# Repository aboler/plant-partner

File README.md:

# plant-partner

Plant Partner repo. for CEN4908c

- **Contributors**: Nicholas Cimino, Aspen Boler, Sabrina Luu, Carter Kreis, Fernando Amado-Pupo
- [Project link](https://github.com/users/aboler/projects/1)

### Notes for adding code and time reports

- Please create a new branch to develop off of main
  - main remains as a minimum viable product branch available
  - Allows PR's to be made for adding to dev so group members can review code made
- Add reports for any changes/development work done in a day in main branch
  - Make reports in Documentation/Reports in relevant timesheet

## Meeting Times

- Meet weekly for ~15 minutes after every client meeting to ensure we're staying on track

## Completed Work

### Hardware Release

Please see ``Documentation/Diagrams``, ``Documentation/Circuits``, and ``Documentation/pcbDesign`` for current hardware designed, built, and used for testing

### Software Release

<ins>For ESP32 (in VSCode):</ins>

1. Run ``git clone recurse-submodules git@github.com:aboler/plant-partner.git``
   - This will clone the base plant-partner and esp-idf Github repositories using ssh
2. Download the ESP-IDF Extension
3. After you install the extension, the  should appear in the VS Code Activity bar (left side set of icons). When you click the Espressif icon, you can see a list of basic commands provided by this extension.
4. From the command list, select Configure ESP-IDF Extension or press F1 and type “Configure ESP-IDF Extension”. After, choose the ESP-IDF: Configure ESP-IDF Extension option.
5. Choose Express. Select Github for the download server.
6. For “Select ESP-IDF version” select “Find ESP-IDF in your system”
7. For “Enter ESP-IDF directory (IDF_PATH):” click the folder icon and within the Github Repository select /plant-partner/microSrc/submodules/esp-idf
8. For “Enter ESP-IDF Tools directory (IDF_TOOLS_PATH):” select the default location or wherever you prefer
   - Make sure that IDF_TOOLS_PATH had no spaces and is not in the Github Repo
9. If your operating system is MacOS/Linux, choose the system Python executable to create ESP-IDF virtual environment inside ESP-IDF Tools and install ESP-IDF Python package there
10. Click Install
11. If everything is installed correctly, you will see a message that all settings have been configured

In Powershell or a Linux terminal preferably:

1. Run ``cd microSrc``
2. Connect an ESP-32 into computer
3. Setup ESP-IDF and flash ESP-32 by running ``python esp.py -p PORT``
   - You may need to use python3 instead of python
   - PORT will be something like COM3 for Windows and /dev/ttyUSB0 for Ubuntu

<ins>For Backend + Database:</ins>

1. Navigate to ``backEndSrc/``
2. Start up the backend server by running ``npm start``, server will be running once these messages are displayed on the terminal
   - "Connected to MongoDB"
   - "Server running on port 8000"

<ins>For Frontend Application:</ins>

In Bash or Powershell

1. Run `cd frontEndSrc`
2. Run `cd frontend`
3. Run `flutter emulators –launch Medium_Phone_API_36.1`
4. Run `flutter pub get`
   * This command is to pull the dependencies
5. Run `flutter run`

### Pre-Alpha Build

- Ability to control GPIO Pins w/ ESP32.
  - i.e. controlling an external light source
  - Existing interfaces that allow modular control for project's purposes
- ADC data acquisition w/ ESP32
  - i.e. reading in value from photoresistor
  - Existing interfaces that allow modular control for project's purposes
- Developed basic structure to collect plant data from sensors
  - 3 uint16_t variables for collecting light, moisture, and nutrient data
- Breadboard implementation of our hardware/software
  - External photoresistor/LED circuit
- Frontend initial skeleton set up for mobile Android app interface
  - Configured Flutter environment and Android Emulator
  - Built a persistent bottom navigation bar (Tasks, Home, Settings)
  - Developed placeholder screens for each tab
  - Tested UI flow and verified emulator functionality
- Implemented locally-hosted database and backend API source code with basic functions
  - Set up MongoDB database that can be hosted locally, currently stores one JSON data model
  - Created Backend App source code with an API via Express.JS that allows for communication with the backend server and database
  - Organized the source code into folders for function controllers, JSON data models, and CRUD routes for easy addition of new functionality

### Prototype Build

- Ability to configure input GPIO Pins w/ ESP32
- Ability to generate a PWM signal
  - i.e. controlling a water pump omtor
- Modularized ADC data acquisition
  - Allows for configuration for both photoresistor and mositure sensor
- Modified breadboard implementation
  - Developed switch circuit to determine when to sample connected sensors/actuate components
  - e.g. water pump control, photoresistor and moisture sensing, LED actuation
- Ability to connect ESP32 to Wi-Fi
  - Allows new plant data to be sent to the database
- Created a test plant on the database
- Connected application and database so application can receive and display plant data to the Home tab
- Created a update button that allows application to display newly updated data from the database
- Beginnings of a PCB to replace external wiring has been started and posted to the repository
- Migrate database to the cloud via MongoDB atlas to allow for easier testing

### Alpha Build

- General clean up/organization in the code
- Modified ADC to be initialized through one function
- Modified main microcontroller loop to activate from one signal (currently a switch)
  - Reads all sensors
  - Activates actuators if needed
  - Sends data to database over Wi-Fi
- Created more permanent physical set up
  - Liquid tanks
  - Motor pumps in liquid tanks with elongated wires
  - Central cup to act as a pot
  - External carrying mechanism to more easily keep everything together
  - Smaller external circuit board
  - DAD program to act as switch, external LED, and proof that fertilizer motor activates when needed

### Beta Build

- Integrated MQTT messages to be sent from database/app. to initiate microcontroller main loop
  - ```plant_partner/act_tog_en```: toggle autocare enable
  - "plant_partner/ack"
    - w/ ```water``` msg.: actuate water pump, read moisture sensor, then report back data to the app.
    - w/ ```light``` msg.: toggle external LED, read photoresistor, then report back data to the app.
    - w/ ```nutrients``` msg.: actuate fertilizer pump
    - no message: read all of the sensors then report the data to the app.
      - If autocare enabled, then also actuate sensors based on if data requires it
- Finished and ordered PCB
- Soldered temporary physical board
- Instantiated and connected rough physical set up assembled in alpha build
- Added additional user features in the application:
  - Ability to toggle autocare and sync it with the microcontroller
  - button for actuating specific actuators
- Developed MQTT message functionality in the database
  - Time-based sample commands
  - Ability for specific actuation 

## Project Architecture

The ESP32 board is set up to interface with sensors to collect real-time environmental and system data. Currently, the microcontroller waits until it receives particular messages through an MQTT client. Depending on the message it can do the following: 1) toggle if autocare is enabled or disabled, 2) samples sensors, communicate data to the app., and actuate (if autocare on), 3) actuate a specific actuator (i.e. LED, water pump, fertilizer pump). These messages are currently being sent from the application while the sensor data is being communicated to the database.

The sensor readings can be reported to the database and displayed on a mobile application, providing users with remote monitoring. To update the data shown on the application, users must press the update button available in the Home tab. Additionally, there's a scheduling tab available where the autocare feature can be toggled as well as three actuator specific buttons for directly affecting specific devices.

### File Structure Summary

- ``microsrc`` : directory containing relevant ESP32 code
  - ``scripts`` : directory containing scripts necessary for setting up ESP-IDF dependencies and environment for device
  - ``src`` : directory containing all developed code for the program and a CMakeLists.txt to help compile
    - ``main`` : contains main program for ESP32 and CMakeLists.txt compiling developed code
    - ``dataTypes`` : contains code defining common data types created for the project, like plantData
    - ``peripherals`` : code for modularizing intercations with certain peripheral systems, like ADC, GPIO, and PWM
    - ``wifi`` : code for implementing wifi communication in the esp32
  - ``submodules`` : directory containing other repositories utilized within the main code
    - ``esp-idf`` : submodule containing examples and ESP32 interfaces in c
  - ``esp.py`` : Python script which can setup, build, flash, and/or monitor ESP-32
- ``backEndSrc`` : directory containing relevant backend code

  - ``controller`` : directory containing code for controllers that implement backend API CRUD functions for the server
    - ``sensorController.js`` : code for implementing CRUD functions that work with JSON data of the Sensor model
  - ``model`` : directory containing code for JSON data models to be used by the backend server and MongoDB database
    - ``sensorModel.js`` : code for creating the JSON Sensor data model
  - ``routes`` : directory containing code for the API's routes that allow CRUD functions to be accessed via URI in an HTTP request
    - ``sensorRoute.js`` : code for the routes that make use of functions that work with the Sensor JSON data model
  - ``node_modules`` : directory containing the node.js dependencies needed to create the backend code
  - ``.env`` : file that holds environment variables to be used by the main code of the backend server, app.js
  - ``app.js`` : the main code of the backend server, connecting to the mongoDB database, linking the routes, and locally hosting server
  - ``package-lock.json`` : the package-lock file for all the node package dependencies needed for the backend server
  - ``package.json`` : the package file listing the basic details and dependencies of the backend server project
- ``frontEndSrc`` : directory containing all Flutter/Dart source code for the mobile application.

  - ``lib``: root directory for all application logic, user interface screens, and services.
    - ``main``: application entry point; initializes the app and launches the bottom navigation shell
    - `nav.dart/dashboard_nav.dart`: bottom navigation bar widget and screen routing logic
    - ``views/``: directory containing all primary UI pages
      - `homeView.dart`: displays live plant sensor data from MongoDB and includes refresh functionality.
      - `taskView.dart/settingsView.dart:` placeholder screen for task/scheduling and user settings
      - `addPlantView.dart`: screen for adding new plants (prototype stage)
    - `services/`: directory for backend communication modules
      - `remote_service.dart`: handles HTTP requests to the backend
    - `plant.dart`: types data model used to decode JSON plant objects from the database

- ``Documentation`` : directory containing relevant project documentation
  - ``Circuits`` : directory containing relevant circuits created during development
  - ``ClassSubmissions`` : directory containing a file with the link to the Google Drive folder containing all of our report work/submissions
  - ``Contributions`` : directory containing all members' timesheet records
  - ``Datasheets`` : directory containing schematics to reference for our current materials being used
  - ``Diagrams`` : directory containing relevant diagrams created during development
  - ``Materials`` : directory containing documentation related to materials, such as which items were purchased and from where
  - ``Mosquitto`` : directory containing configuration files needed to successfully run mosquitto with our program
  - ``Research`` : directory containing research collected during the project, such as how to set up a coding environment for the ESP32
  - ``pcbDesign`` : directory containing work dones towards designing/building our project's PCB

## How to Use esp.py

PORT: This is USB port that the ESP-32 is connected to. For Windows, it should be COM3 or something similar. For Ubuntu, it should be ``/dev/ttyUSB0`` or something similar. Be aware, that if the Port is not automatically detected (usually Windows) you may have to install a driver being Silicon Labs CP210x or FTDI.

- Default: ``python esp.py -p PORT``
  - This will run the necessary setup scripts to install the ESP-IDF dependencies then build, flash, and monitor the ESP-32 at PORT
- Build: ``python esp.py build``
  - This will only build the current code under microSrc/src
- Flash: ``python esp.py flash -p PORT``
  - This will build and flash the current code under microSrc/src onto the ESP-32 at the connected Port
- Monitor: ``python esp.py monitor -p PORT``
  - This will monitor the ESP-32 at the connected Port and fill the terminal with any outputs from the ESP-32
- Clean: ``python esp.py clean``
  - This will delete any build artifacts

N.B. You may have to use python3 instead of python

## Current Bugs:

The system is in a development state with only base-level functionality implemented. No bugs reported

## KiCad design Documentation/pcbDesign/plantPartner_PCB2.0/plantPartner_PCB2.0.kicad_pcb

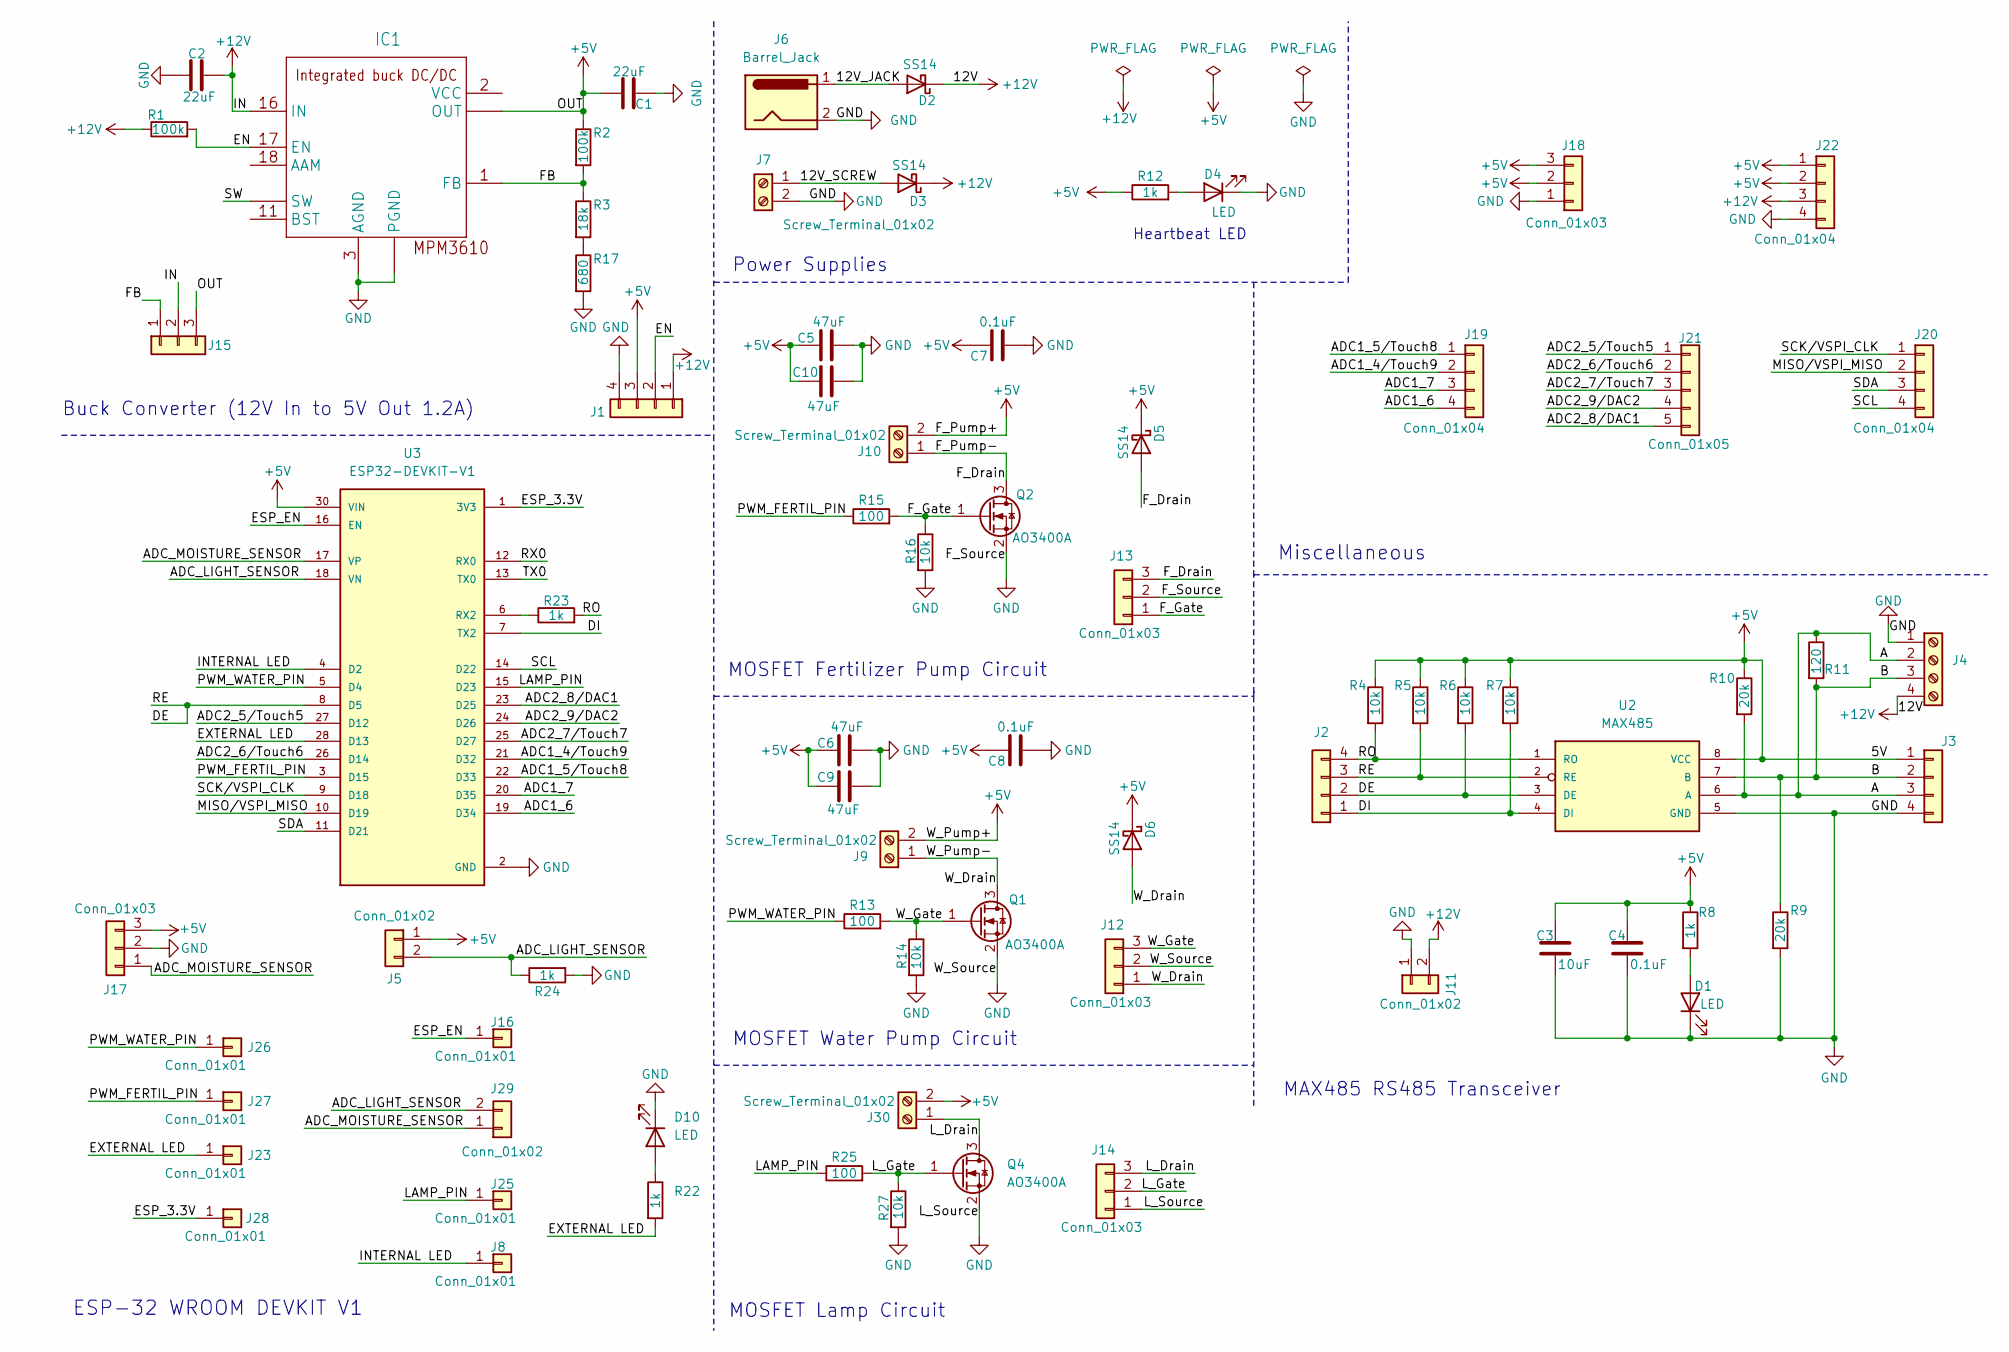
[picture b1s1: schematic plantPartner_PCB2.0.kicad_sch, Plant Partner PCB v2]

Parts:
C1, C2: 22uF; C_0603_1608Metric
C3: 10uF; C_0402_1005Metric
C4: 0.1uF; C_0402_1005Metric
C5, C6, C9, C10: 47uF; C_0805_2012Metric
C7, C8: 0.1uF; C_0603_1608Metric
D1, D4, D10: LED; LED_0603_1608Metric
D2, D3, D5, D6: SS14; D_SMA
IC1: MPM3610
J1, J2, J3, J19, J20, J22: Conn_01x04; PinHeader_1x04_P2.54mm_Vertical
J4: Screw_Terminal_01x04; TerminalBlock_Phoenix_MPT-0,5-4-2.54_1x04_P2.54mm_Horizontal
J5, J11, J29: Conn_01x02; PinHeader_1x02_P2.54mm_Vertical
J6: Barrel_Jack; BarrelJack_GCT_DCJ200-10-A_Horizontal
J7, J9, J10, J30: Screw_Terminal_01x02; TerminalBlock_Phoenix_MPT-0,5-2-2.54_1x02_P2.54mm_Horizontal
J8, J16, J23, J25, J26, J27, J28: Conn_01x01; PinHeader_1x01_P2.54mm_Vertical
J12, J13, J14, J15, J17, J18: Conn_01x03; PinHeader_1x03_P2.54mm_Vertical
J21: Conn_01x05; PinHeader_1x05_P2.54mm_Vertical
Q1, Q2, Q4: AO3400A; SOT-23
R1, R2: 100k; R_0402_1005Metric
R3: 18k; R_0603_1608Metric
R4, R5, R6, R7, R14, R16, R27: 10k; R_0402_1005Metric
R8, R12, R22, R23, R24: 1k; R_0402_1005Metric
R9, R10: 20k; R_0402_1005Metric
R11: 120; R_0402_1005Metric
R13, R15, R25: 100; R_0402_1005Metric
R17: 680; R_0603_1608Metric
U2: MAX485; SO08
U3: ESP32-DEVKIT-V1; MODULE_ESP32_DEVKIT_V1; PARTREV N/A

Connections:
+5V: C1.1, C3.1, C4.1, C5.1, C6.1, C7.1, C8.1, C9.1, C10.1, D5.1 (K), D6.1 (K), IC1.7 (OUT), IC1.8 (OUT), IC1.9 (OUT), J1.3, J3.1, J5.1, J9.2, J10.2, J15.3, J17.3, J18.2, J18.3, J22.1, J22.2, J30.2, R2.1, R4.1, R5.1, R6.1, R7.1, R8.1, R10.1, R12.1, U2.8 (VCC), U3.30 (VIN)
+12V: C2.1, D2.1 (K), D3.1 (K), IC1.16 (IN), J1.1, J4.4, J11.2, J15.2, J22.3, R1.1
/12V_JACK: D2.2 (A), J6.1
/12V_SCREW: D3.2 (A), J7.1
/A: J3.3, J4.2, R10.2, R11.1, U2.6 (A)
/ADC1_4/Touch9: J19.2, U3.21 (D32)
/ADC1_5/Touch8: J19.1, U3.22 (D33)
/ADC1_6: J19.4, U3.19 (D34)
/ADC1_7: J19.3, U3.20 (D35)
/ADC2_5/Touch5: J21.1, U3.27 (D12)
/ADC2_6/Touch6: J21.2, U3.26 (D14)
/ADC2_7/Touch7: J21.3, U3.25 (D27)
/ADC2_8/DAC1: J21.5, U3.23 (D25)
/ADC2_9/DAC2: J21.4, U3.24 (D26)
/ADC_LIGHT_SENSOR: J5.2, J29.2, R24.1, U3.18 (VN)
/ADC_MOISTURE_SENSOR: J17.1, J29.1, U3.17 (VP)
/B: J3.2, J4.3, R9.1, R11.2, U2.7 (B)
/DE: J2.2, J2.3, R5.2, R6.2, U2.2 (RE), U2.3 (DE), U3.8 (D5)
/DI: J2.1, R7.2, U2.4 (DI), U3.7 (TX2)
/EN: IC1.17 (EN), J1.2, R1.2
/ESP_3.3V: J28.1, U3.1 (3V3)
/ESP_EN: J16.1, U3.16 (EN)
/EXTERNAL LED: J23.1, R22.2, U3.28 (D13)
/FB: IC1.1 (FB), J15.1, R2.2, R3.1
/F_Drain: D5.2 (A), J10.1, J13.3, Q2.3 (D)
/F_Gate: J13.1, Q2.1 (G), R15.2, R16.1
/INTERNAL LED: J8.1, U3.4 (D2)
/LAMP_PIN: J25.1, R25.1, U3.15 (D23)
/L_Drain: J14.3, J30.1, Q4.3 (D)
/L_Gate: J14.2, Q4.1 (G), R25.2, R27.1
/MISO/VSPI_MISO: J20.2, U3.10 (D19)
/PWM_FERTIL_PIN: J27.1, R15.1, U3.3 (D15)
/PWM_WATER_PIN: J26.1, R13.1, U3.5 (D4)
/RO: J2.4, R4.2, R23.2, U2.1 (RO)
/RX0: U3.12 (RX0)
/SCK/VSPI_CLK: J20.1, U3.9 (D18)
/SCL: J20.4, U3.14 (D22)
/SDA: J20.3, U3.11 (D21)
/SW: IC1.4 (SW), IC1.5 (SW), IC1.6 (SW)
/TX0: U3.13 (TX0)
/W_Drain: D6.2 (A), J9.1, J12.1, Q1.3 (D)
/W_Gate: J12.3, Q1.1 (G), R13.2, R14.1
GND: C1.2, C2.2, C3.2, C4.2, C5.2, C6.2, C7.2, C8.2, C9.2, C10.2, D1.1 (K), D4.1 (K), D10.1 (K), IC1.3 (AGND), IC1.12 (PGND), IC1.13 (PGND), IC1.14 (PGND), J1.4, J3.4, J4.1, J6.2, J7.2, J11.1, J12.2, J13.2, J14.1, J17.2, J18.1, J22.4, Q1.2 (S), Q2.2 (S), Q4.2 (S), R9.2, R14.2, R16.2, R17.2, R24.2, R27.2, U2.5 (GND), U3.2 (GND), U3.29 (GND)
unnamed: D1.2 (A), R8.2
unnamed: D4.2 (A), R12.2
unnamed: D10.2 (A), R22.1
unnamed: R3.2, R17.1
unnamed: R23.1, U3.6 (RX2)

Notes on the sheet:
Heartbeat LED
Power Supplies
ESP-32 WROOM DEVKIT V1
Miscellaneous
MAX485 RS485 Transceiver
Buck Converter (12V In to 5V Out 1.2A)
MOSFET Water Pump Circuit
MOSFET Fertilizer Pump Circuit
MOSFET Lamp Circuit

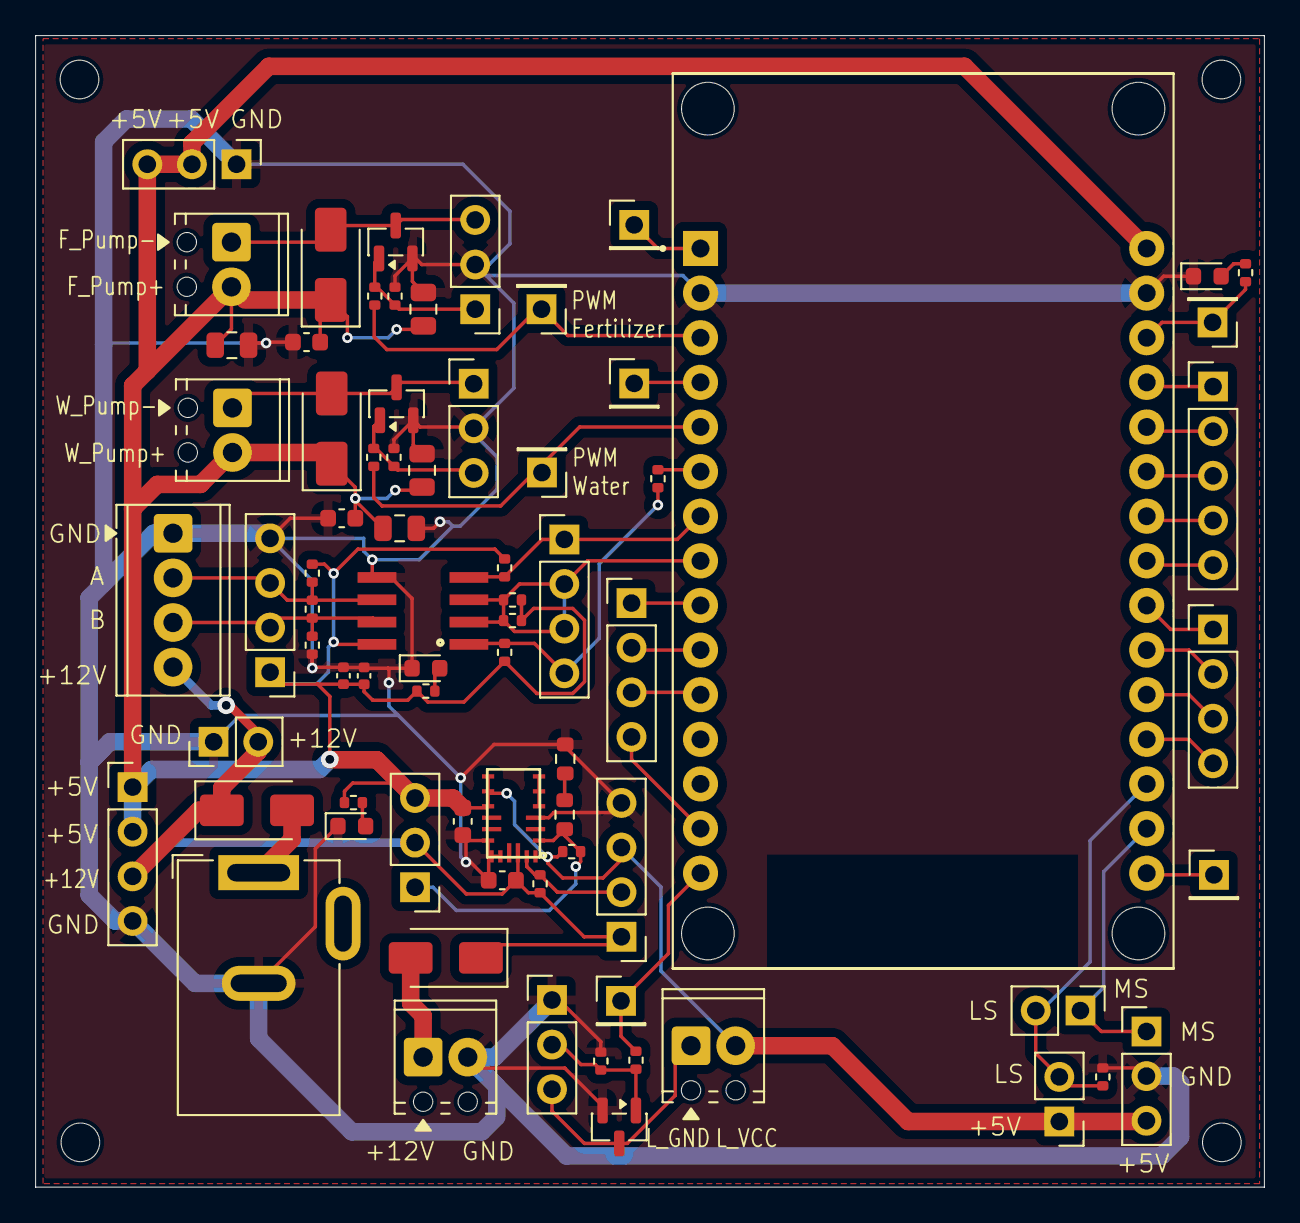
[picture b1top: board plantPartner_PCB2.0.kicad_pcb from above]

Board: 2 copper layers, 70.0 x 65.5 mm, 74 parts (0 on the bottom side), 46 nets.

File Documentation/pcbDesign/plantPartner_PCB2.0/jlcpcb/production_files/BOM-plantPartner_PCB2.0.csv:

Comment,Designator,Footprint,LCSC,Quantity
0.1uF,"C7,C8",C_0603_1608Metric,C14663,2
0.1uF,C4,C_0402_1005Metric,C1525,1
100,"R13,R15,R25",R_0402_1005Metric,C25076,3
100k,"R1,R2",R_0402_1005Metric,C25741,2
10k,"R14,R16,R27,R4,R5,R6,R7",R_0402_1005Metric,C25744,7
10uF,C3,C_0402_1005Metric,C15525,1
120,R11,R_0402_1005Metric,C25079,1
18k,R3,R_0603_1608Metric,C25810,1
1k,"R12,R22,R23,R24,R8",R_0402_1005Metric,C11702,5
20k,"R10,R9",R_0402_1005Metric,C25765,2
220uF,"C5,C6",C_0603_1608Metric,C2163637,2
22uF,"C1,C2",C_0603_1608Metric,C59461,2
680,R17,R_0603_1608Metric,C23228,1
AO3400A,"Q1,Q2,Q4",SOT-23,C20917,3
LED,"D1,D10,D4",LED_0603_1608Metric,C2286,3
MAX485,U2,SO08,C19738,1
MPM3610,IC1,MPM3610,C5173872,1
SS14,"D2,D3,D5,D6",D_SMA,C2480,4
ESP32-DEVKIT-V1,U3,MODULE_ESP32_DEVKIT_V1,,1
Screw_Terminal_01x02,J30,"TerminalBlock_Phoenix_MPT-0,5-2-2.54_1x02_P2.54mm_Horizontal",,1
Conn_01x02,J29,PinHeader_1x02_P2.54mm_Vertical,,1
Conn_01x01,J28,PinHeader_1x01_P2.54mm_Vertical,,1
Conn_01x01,J27,PinHeader_1x01_P2.54mm_Vertical,,1
Conn_01x01,J26,PinHeader_1x01_P2.54mm_Vertical,,1
Conn_01x01,J25,PinHeader_1x01_P2.54mm_Vertical,,1
Conn_01x01,J23,PinHeader_1x01_P2.54mm_Vertical,,1
Conn_01x04,J22,PinHeader_1x04_P2.54mm_Vertical,,1
Conn_01x05,J21,PinHeader_1x05_P2.54mm_Vertical,,1
Conn_01x04,J20,PinHeader_1x04_P2.54mm_Vertical,,1
Conn_01x03,J17,PinHeader_1x03_P2.54mm_Vertical,,1
Conn_01x01,J16,PinHeader_1x01_P2.54mm_Vertical,,1
Conn_01x02,J11,PinHeader_1x02_P2.54mm_Vertical,,1
Screw_Terminal_01x02,J10,"TerminalBlock_Phoenix_MPT-0,5-2-2.54_1x02_P2.54mm_Horizontal",,1
Screw_Terminal_01x02,J9,"TerminalBlock_Phoenix_MPT-0,5-2-2.54_1x02_P2.54mm_Horizontal",,1
Conn_01x01,J8,PinHeader_1x01_P2.54mm_Vertical,,1
Screw_Terminal_01x02,J7,"TerminalBlock_Phoenix_MPT-0,5-2-2.54_1x02_P2.54mm_Horizontal",,1
Barrel_Jack,J6,BarrelJack_GCT_DCJ200-10-A_Horizontal,,1
Conn_01x02,J5,PinHeader_1x02_P2.54mm_Vertical,,1
Screw_Terminal_01x04,J4,"TerminalBlock_Phoenix_MPT-0,5-4-2.54_1x04_P2.54mm_Horizontal",,1
Conn_01x04,J3,PinHeader_1x04_P2.54mm_Vertical,,1
Conn_01x04,J2,PinHeader_1x04_P2.54mm_Vertical,,1
Conn_01x04,J1,PinHeader_1x04_P2.54mm_Vertical,,1
Conn_01x03,J13,PinHeader_1x03_P2.54mm_Vertical,,1
Conn_01x03,J12,PinHeader_1x03_P2.54mm_Vertical,,1
Conn_01x03,J14,PinHeader_1x03_P2.54mm_Vertical,,1
Conn_01x03,J18,PinHeader_1x03_P2.54mm_Vertical,,1
Conn_01x03,J15,PinHeader_1x03_P2.54mm_Vertical,,1
Conn_01x04,J19,PinHeader_1x04_P2.54mm_Vertical,,1

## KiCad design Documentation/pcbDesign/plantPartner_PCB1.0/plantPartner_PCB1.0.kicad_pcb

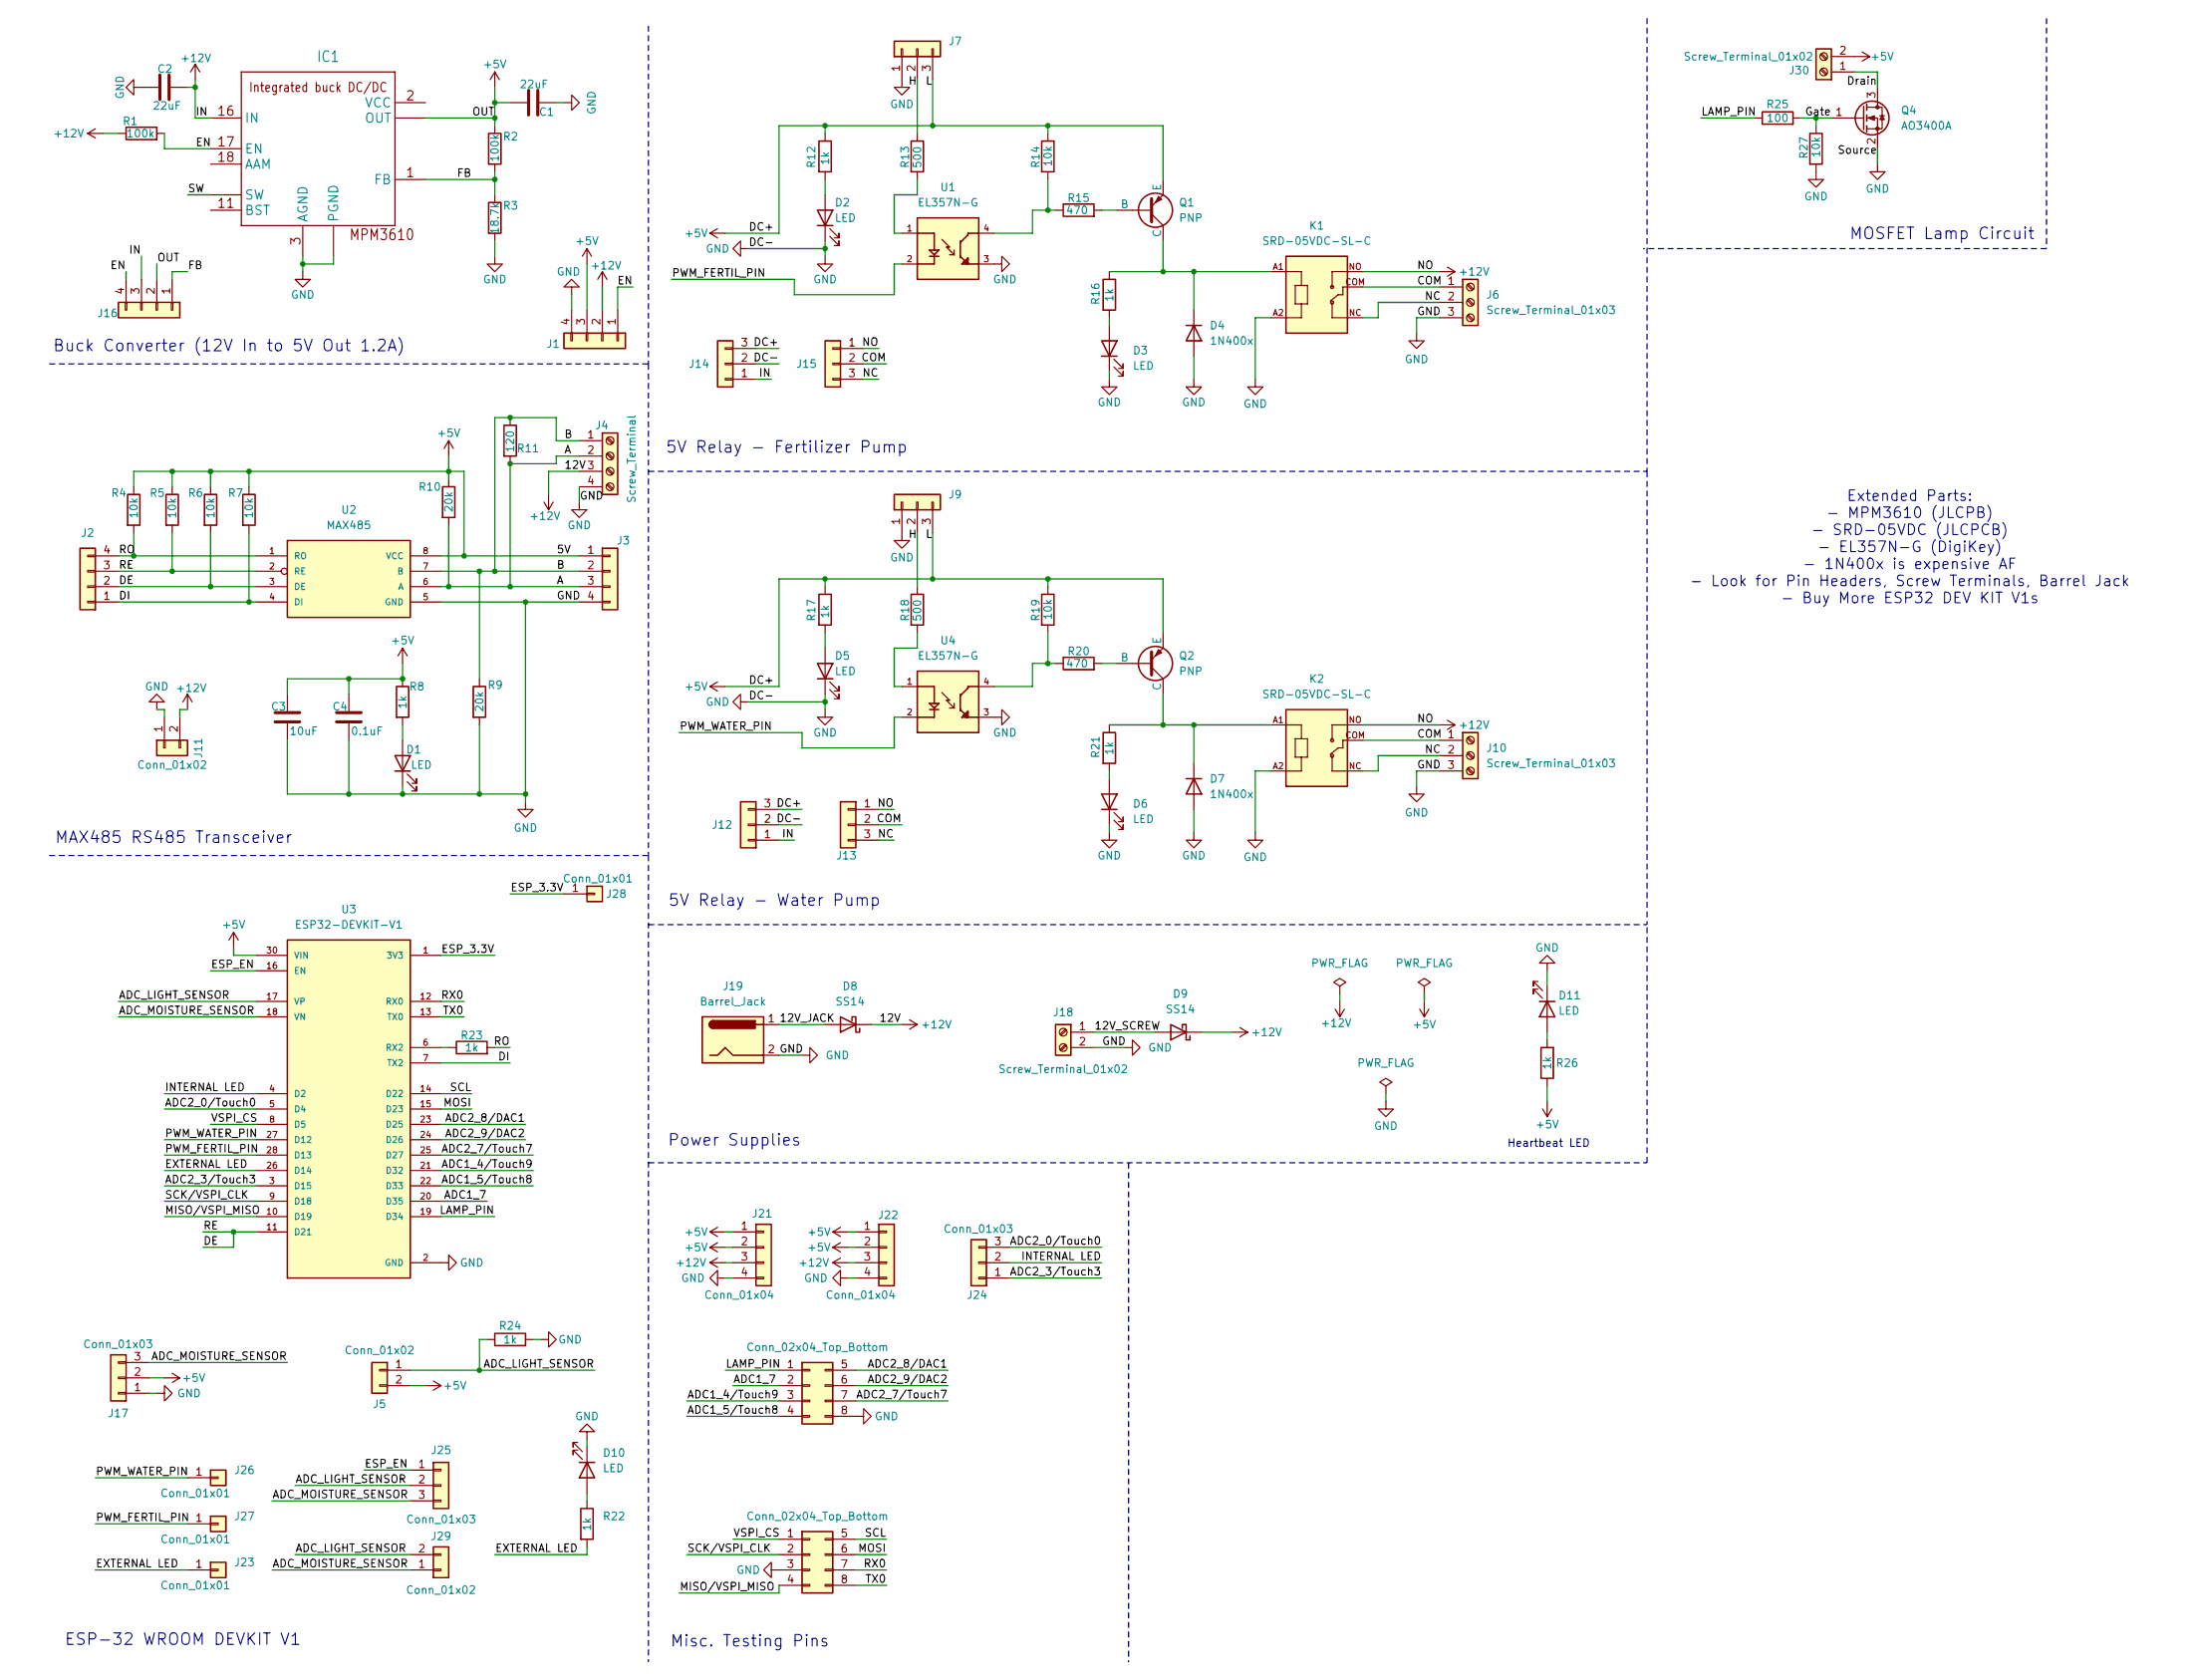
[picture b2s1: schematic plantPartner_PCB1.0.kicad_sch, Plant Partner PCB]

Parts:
C1, C2: 22uF; C_0603_1608Metric
C3: 10uF; C_0402_1005Metric
C4: 0.1uF; C_0402_1005Metric
D1, D2, D3, D5, D6, D10, D11: LED; LED_0603_1608Metric
D4, D7: 1N400x; D_A-405_P7.62mm_Horizontal
D8, D9: SS14; D_SMA
IC1: MPM3610
J1, J2, J3, J16, J21, J22: Conn_01x04; PinHeader_1x04_P2.54mm_Vertical
J4: Screw_Terminal; TerminalBlock_Phoenix_MKDS-1,5-4-5.08_1x04_P5.08mm_Horizont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
J5, J11, J29: Conn_01x02; PinHeader_1x02_P2.54mm_Vertical
J6, J10: Screw_Terminal_01x03; TerminalBlock_Phoenix_MKDS-1,5-3-5.08_1x03_P5.08mm_Horizont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
J7, J9, J12, J13, J14, J15, J17, J24, J25: Conn_01x03; PinHeader_1x03_P2.54mm_Vertical
J8, J20: Conn_02x04_Top_Bottom; PinHeader_2x04_P2.54mm_Vertical
J18, J30: Screw_Terminal_01x02; TerminalBlock_Phoenix_MKDS-1,5-2-5.08_1x02_P5.08mm_Horizont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
J19: Barrel_Jack; BarrelJack_GCT_DCJ200-10-A_Horizontal
J23, J26, J27, J28: Conn_01x01; PinHeader_1x01_P2.54mm_Vertical
K1, K2: SRD-05VDC-SL-C; RELAY_SRD-05VDC-SL-C
Q1, Q2: PNP; TO-92
Q4: AO3400A; SOT-23
R1, R2: 100k; R_0402_1005Metric
R3: 18.7k; R_0603_1608Metric
R4, R5, R6, R7, R14, R19, R27: 10k; R_0402_1005Metric
R8, R12, R16, R17, R21, R22, R23, R24, R26: 1k; R_0402_1005Metric
R9, R10: 20k; R_0402_1005Metric
R11: 120; R_0402_1005Metric
R13, R18: 500; R_0603_1608Metric
R15, R20: 470; R_0402_1005Metric
R25: 100; R_0402_1005Metric
U1, U4: EL357N-G; OPTO_EL357N-G; PARTREV 6
U2: MAX485; SO08
U3: ESP32-DEVKIT-V1; MODULE_ESP32_DEVKIT_V1; PARTREV N/A

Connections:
+5V: C1.1, C3.1, C4.1, IC1.7 (OUT), IC1.8 (OUT), IC1.9 (OUT), J1.3, J3.1, J5.2, J7.3, J9.3, J12.3, J14.3, J16.2, J17.2, J21.1, J21.2, J22.1, J22.2, J30.2, Q1.3 (E), Q2.3 (E), R2.1, R4.1, R5.1, R6.1, R7.1, R8.1, R10.1, R12.1, R14.1, R17.1, R19.1, R26.1, U2.8 (VCC), U3.30 (VIN)
+12V: C2.1, D8.1 (K), D9.1 (K), IC1.16 (IN), J1.2, J4.3, J11.2, J12.1, J13.1, J14.1, J15.1, J16.3, J21.3, J22.3, K1.NO, K2.NO, R1.1
/12V_JACK: D8.2 (A), J19.1
/12V_SCREW: D9.2 (A), J18.1
/A: J3.3, J4.2, R10.2, R11.2, U2.6 (A)
/ADC1_4/Touch9: J20.3, U3.21 (D32)
/ADC1_5/Touch8: J20.4, U3.22 (D33)
/ADC1_7: J20.2, U3.20 (D35)
/ADC2_0/Touch0: J24.3, U3.5 (D4)
/ADC2_3/Touch3: J24.1, U3.3 (D15)
/ADC2_7/Touch7: J20.7, U3.25 (D27)
/ADC2_8/DAC1: J20.5, U3.23 (D25)
/ADC2_9/DAC2: J20.6, U3.24 (D26)
/ADC_LIGHT_SENSOR: J5.1, J25.2, J29.2, R24.1, U3.17 (VP)
/ADC_MOISTURE_SENSOR: J17.3, J25.3, J29.1, U3.18 (VN)
/B: J3.2, J4.1, R9.1, R11.1, U2.7 (B)
/COM: J6.1, J10.1, J13.2, J15.2, K1.COM, K2.COM
/DE: J2.2, J2.3, R5.2, R6.2, U2.2 (RE), U2.3 (DE), U3.11 (D21)
/DI: J2.1, R7.2, U2.4 (DI), U3.7 (TX2)
/Drain: J30.1, Q4.3 (D)
/EN: IC1.17 (EN), J1.1, J16.4, R1.2
/ESP_3.3V: J28.1, U3.1 (3V3)
/ESP_EN: J25.1, U3.16 (EN)
/EXTERNAL LED: J23.1, R22.2, U3.26 (D14)
/FB: IC1.1 (FB), J16.1, R2.2, R3.1
/Gate: Q4.1 (G), R25.2, R27.1
/H: J7.2, J9.2, R13.1, R18.1
/INTERNAL LED: J24.2, U3.4 (D2)
/LAMP_PIN: J20.1, R25.1, U3.19 (D34)
/MISO/VSPI_MISO: J8.4, U3.10 (D19)
/MOSI: J8.6, U3.15 (D23)
/NC: J6.2, J10.2, J13.3, J15.3, K1.NC, K2.NC
/PWM_FERTIL_PIN: J27.1, U1.2, U3.28 (D13)
/PWM_WATER_PIN: J26.1, U3.27 (D12), U4.2
/RO: J2.4, R4.2, R23.2, U2.1 (RO)
/RX0: J8.7, U3.12 (RX0)
/SCK/VSPI_CLK: J8.2, U3.9 (D18)
/SCL: J8.5, U3.14 (D22)
/SW: IC1.4 (SW), IC1.5 (SW), IC1.6 (SW)
/TX0: J8.8, U3.13 (TX0)
/VSPI_CS: J8.1, U3.8 (D5)
GND: C1.2, C2.2, C3.2, C4.2, D1.1 (K), D2.1 (K), D3.1 (K), D4.2 (A), D5.1 (K), D6.1 (K), D7.2 (A), D10.1 (K), D11.1 (K), IC1.3 (AGND), IC1.12 (PGND), IC1.13 (PGND), IC1.14 (PGND), J1.4, J3.4, J4.4, J6.3, J7.1, J8.3, J9.1, J10.3, J11.1, J12.2, J14.2, J17.1, J18.2, J19.2, J20.8, J21.4, J22.4, K1.A2, K2.A2, Q4.2 (S), R3.2, R9.2, R24.2, R27.2, U1.3, U2.5 (GND), U3.2 (GND), U3.29 (GND), U4.3
unnamed: D1.2 (A), R8.2
unnamed: D2.2 (A), R12.2
unnamed: D3.2 (A), R16.2
unnamed: D4.1 (K), K1.A1, Q1.1 (C), R16.1
unnamed: D5.2 (A), R17.2
unnamed: D6.2 (A), R21.2
unnamed: D7.1 (K), K2.A1, Q2.1 (C), R21.1
unnamed: D10.2 (A), R22.1
unnamed: D11.2 (A), R26.2
unnamed: Q1.2 (B), R15.2
unnamed: Q2.2 (B), R20.2
unnamed: R13.2, U1.1
unnamed: R14.2, R15.1, U1.4
unnamed: R18.2, U4.1
unnamed: R19.2, R20.1, U4.4
unnamed: R23.1, U3.6 (RX2)

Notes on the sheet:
Extended Parts: - MPM3610 (JLCPB) - SRD-05VDC (JLCPCB) - EL357N-G (DigiKey) - 1N400x is expensive AF - Look for Pin Headers, Screw Terminals, Barrel Jack - Buy More ESP32 DEV KIT V1s
Buck Converter (12V In to 5V Out 1.2A)
ESP-32 WROOM DEVKIT V1
Misc. Testing Pins
5V Relay - Fertilizer Pump
Power Supplies
5V Relay - Water Pump
MOSFET Lamp Circuit
MAX485 RS485 Transceiver
Heartbeat LED

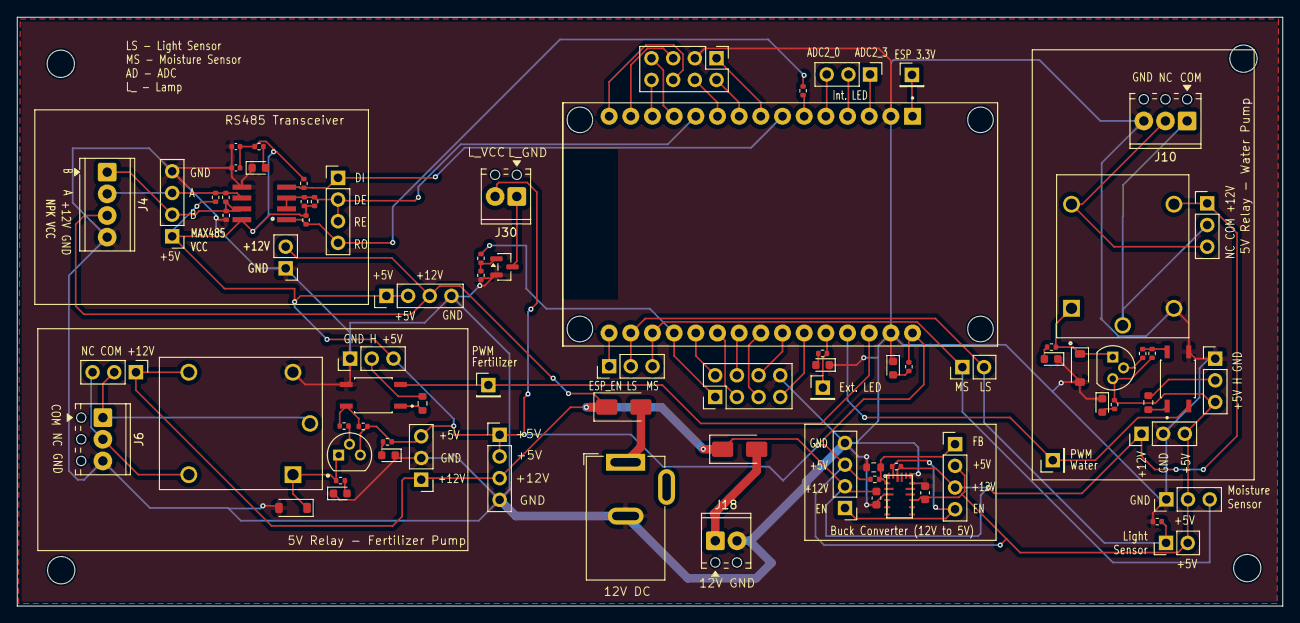
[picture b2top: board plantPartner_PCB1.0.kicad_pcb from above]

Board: 2 copper layers, 148.3 x 69.0 mm, 86 parts (0 on the bottom side), 58 nets.

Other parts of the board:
BottomLeft: MountingHole_3.2mm_M3
BottomRight: MountingHole_3.2mm_M3
TopLeft: MountingHole_3.2mm_M3
TopRight: MountingHole_3.2mm_M3

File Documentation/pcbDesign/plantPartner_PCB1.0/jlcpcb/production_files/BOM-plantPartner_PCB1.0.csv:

Comment,Designator,Footprint,LCSC,Quantity
0.1uF,C4,C_0402_1005Metric,C1525,1
100,R25,R_0402_1005Metric,C25076,1
100k,"R1,R2",R_0402_1005Metric,C25741,2
10k,"R14,R19,R27,R4,R5,R6,R7",R_0402_1005Metric,C25744,7
10uF,C3,C_0402_1005Metric,C15525,1
120,R11,R_0402_1005Metric,C25079,1
1k,"R12,R16,R17,R21,R22,R23,R24,R26,R8",R_0402_1005Metric,C11702,9
20k,"R10,R9",R_0402_1005Metric,C25765,2
22uF,"C1,C2",C_0603_1608Metric,C59461,2
470,"R15,R20",R_0402_1005Metric,C25117,2
AO3400A,Q4,SOT-23,C20917,1
LED,"D1,D10,D11,D2,D3,D5,D6",LED_0603_1608Metric,C2286,7
PNP,"Q1,Q2",TO-92,C8326,2
SS14,"D8,D9",D_SMA,C2480,2
Conn_02x04_Top_Bottom,J20,PinHeader_2x04_P2.54mm_Vertical,,1
500,R13,R_0603_1608Metric,,1
Screw_Terminal_01x02,J30,"TerminalBlock_Phoenix_MKDS-1,5-2-5.08_1x02_P5.08mm_Horizontal",,1
Conn_01x04,J1,PinHeader_1x04_P2.54mm_Vertical,,1
Screw_Terminal,J4,"TerminalBlock_Phoenix_MKDS-1,5-4-5.08_1x04_P5.08mm_Horizontal",,1
Conn_01x04,J16,PinHeader_1x04_P2.54mm_Vertical,,1
Conn_01x02,J11,PinHeader_1x02_P2.54mm_Vertical,,1
Conn_02x04_Top_Bottom,J8,PinHeader_2x04_P2.54mm_Vertical,,1
Conn_01x01,J27,PinHeader_1x01_P2.54mm_Vertical,,1
Conn_01x04,J22,PinHeader_1x04_P2.54mm_Vertical,,1
1N400x,D4,D_A-405_P7.62mm_Horizontal,,1
Conn_01x02,J29,PinHeader_1x02_P2.54mm_Vertical,,1
MAX485,U2,SO08,,1
Conn_01x04,J3,PinHeader_1x04_P2.54mm_Vertical,,1
Conn_01x01,J26,PinHeader_1x01_P2.54mm_Vertical,,1
SRD-05VDC-SL-C,K2,RELAY_SRD-05VDC-SL-C,,1
Conn_01x04,J2,PinHeader_1x04_P2.54mm_Vertical,,1
Conn_01x02,J5,PinHeader_1x02_P2.54mm_Vertical,,1
Conn_01x03,J24,PinHeader_1x03_P2.54mm_Vertical,,1
EL357N-G,U4,OPTO_EL357N-G,,1
Conn_01x03,J9,PinHeader_1x03_P2.54mm_Vertical,,1
18.7k,R3,R_0603_1608Metric,,1
Conn_01x03,J25,PinHeader_1x03_P2.54mm_Vertical,,1
500,R18,R_0603_1608Metric,,1
Conn_01x03,J14,PinHeader_1x03_P2.54mm_Vertical,,1
Conn_01x03,J12,PinHeader_1x03_P2.54mm_Vertical,,1
Conn_01x03,J17,PinHeader_1x03_P2.54mm_Vertical,,1
Conn_01x04,J21,PinHeader_1x04_P2.54mm_Vertical,,1
Screw_Terminal_01x03,J6,"TerminalBlock_Phoenix_MKDS-1,5-3-5.08_1x03_P5.08mm_Horizontal",,1
Conn_01x03,J7,PinHeader_1x03_P2.54mm_Vertical,,1
MPM3610,IC1,MPM3610,,1
Screw_Terminal_01x02,J18,"TerminalBlock_Phoenix_MKDS-1,5-2-5.08_1x02_P5.08mm_Horizontal",,1
Conn_01x01,J28,PinHeader_1x01_P2.54mm_Vertical,,1
ESP32-DEVKIT-V1,U3,MODULE_ESP32_DEVKIT_V1,,1
1N400x,D7,D_A-405_P7.62mm_Horizontal,,1
SRD-05VDC-SL-C,K1,RELAY_SRD-05VDC-SL-C,,1
Conn_01x03,J15,PinHeader_1x03_P2.54mm_Vertical,,1
Conn_01x03,J13,PinHeader_1x03_P2.54mm_Vertical,,1
Conn_01x01,J23,PinHeader_1x01_P2.54mm_Vertical,,1
Screw_Terminal_01x03,J10,"TerminalBlock_Phoenix_MKDS-1,5-3-5.08_1x03_P5.08mm_Horizontal",,1
Barrel_Jack,J19,BarrelJack_GCT_DCJ200-10-A_Horizontal,,1
EL357N-G,U1,OPTO_EL357N-G,,1
